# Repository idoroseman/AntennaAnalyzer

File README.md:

# Antenna Analyzer

The antenna analyzer will provide VSWR measurements for any antenna from 1 to 30 MHz. 
Frequency and VSWR are shown as a graph on the graphical display, as well as the minimum 
VSWR value and frequency.
The analyzer can be programmed to scan any sub band and has built in ranges for 160m, 80m, 60m, 40m, 30m, 20m, 17m, 15m, 12m, 10m. 

Derivative work of K6BEZ [project website](http://www.360workbench.com/) 

more details about construction on [my website](http://idoroseman.com/?p=841)

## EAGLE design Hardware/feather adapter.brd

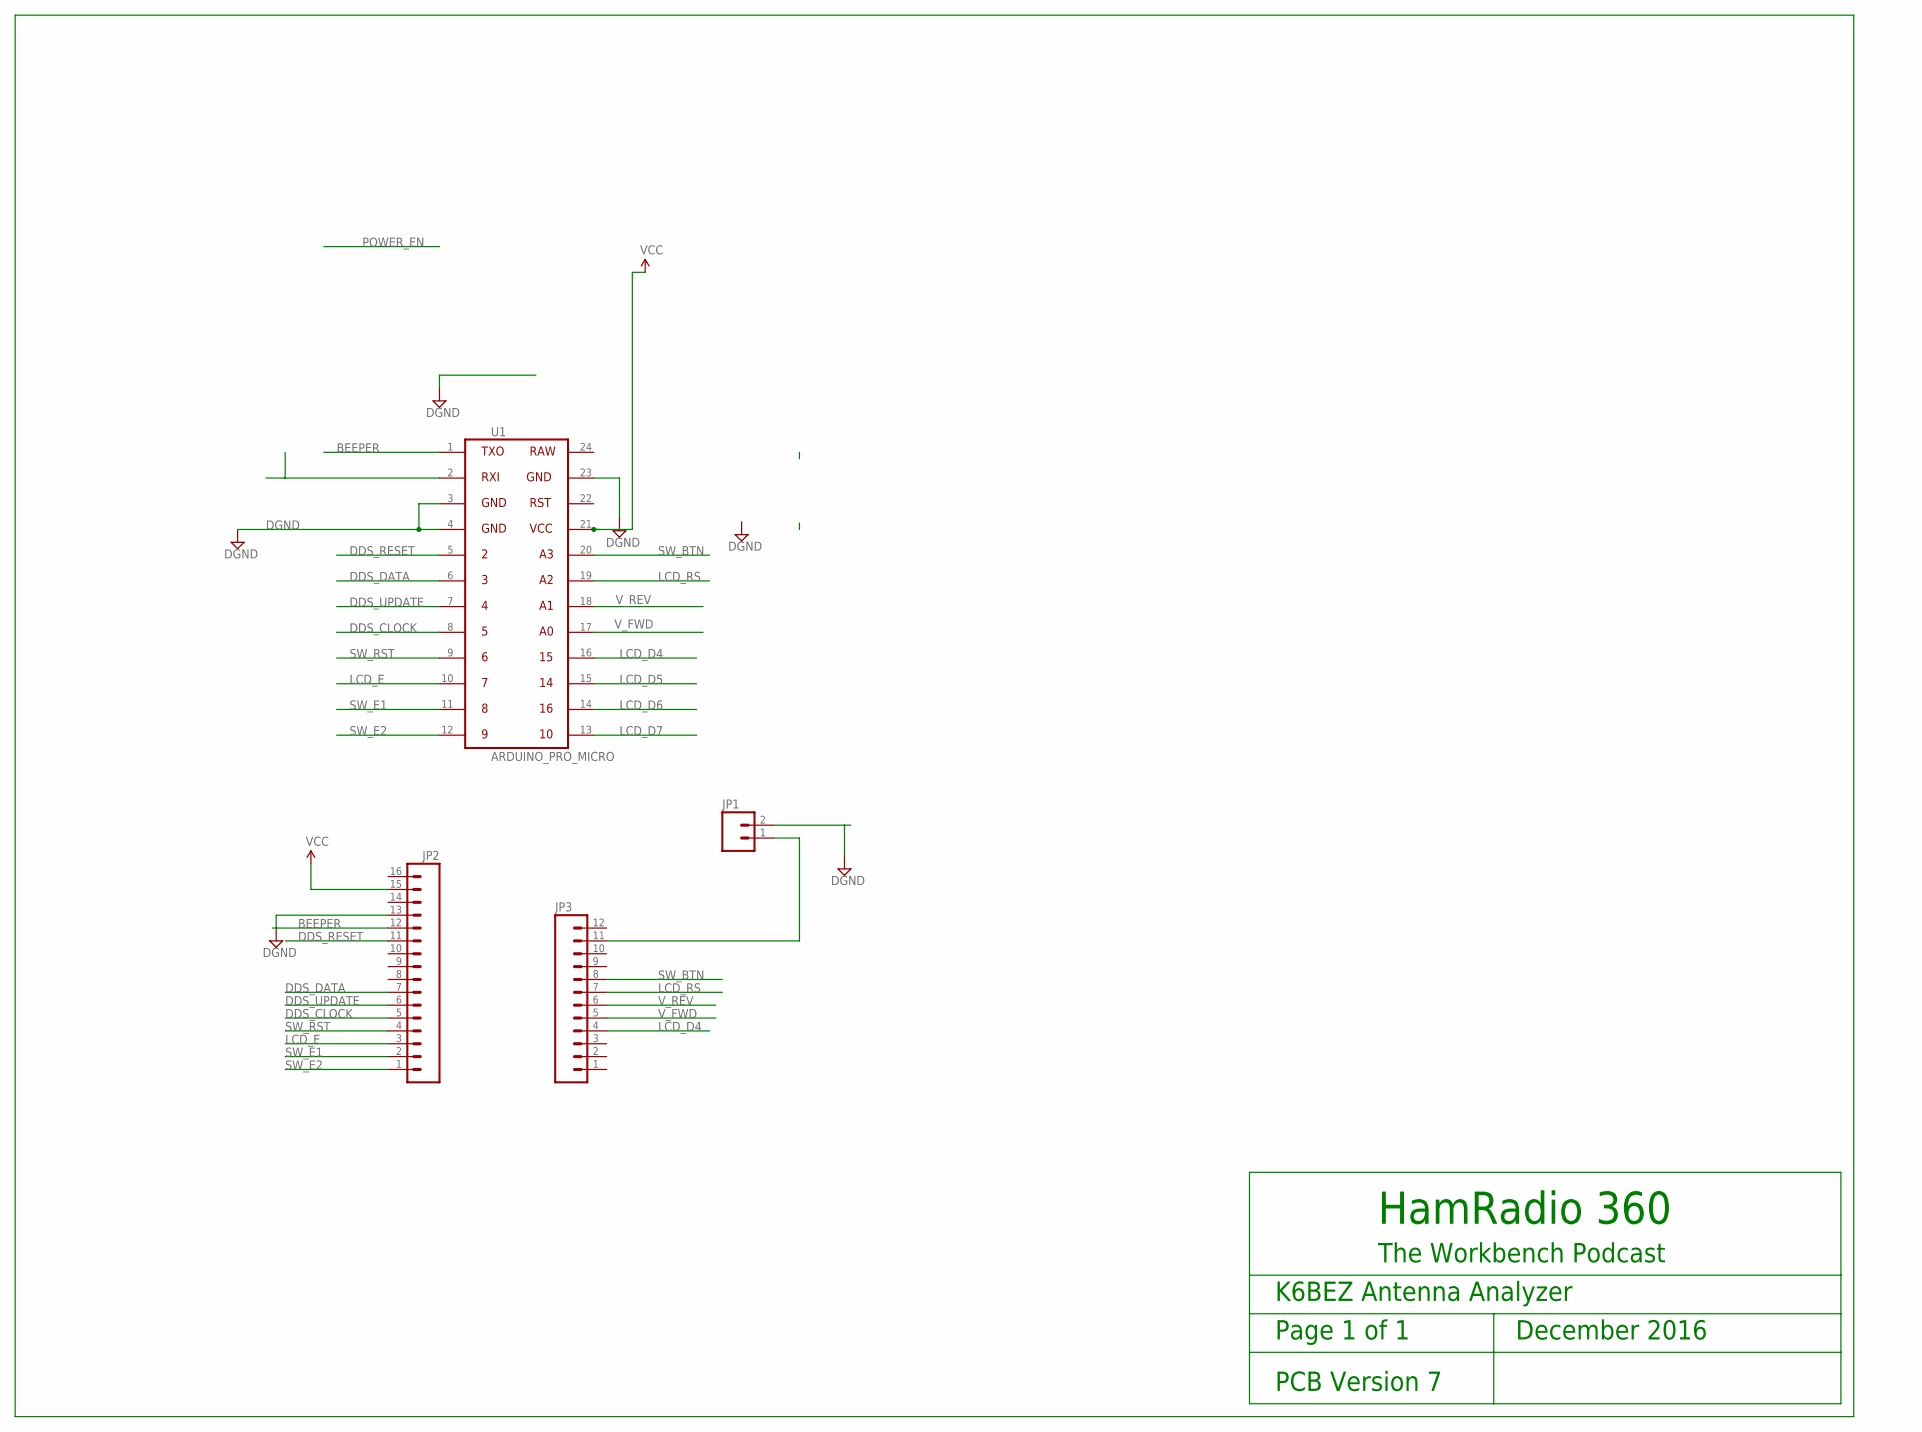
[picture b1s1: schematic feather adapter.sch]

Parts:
JP1: M02PTH; 1X02
JP2: M16PTH; 1X16
JP3: M12PTH; 1X12
U1: ARDUINO_PRO_MICRO

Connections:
BEEPER: JP2.12, U1.1
DDS_CLOCK: JP2.5, U1.8
DDS_DATA: JP2.7, U1.6
DDS_RESET: JP2.11, U1.5
DDS_UPDATE: JP2.6, U1.7
DGND: JP1.2, JP2.13, U1.3, U1.4, U1.23
LCD_D4: JP3.4, U1.16
LCD_D5: U1.15
LCD_D6: U1.14
LCD_D7: U1.13
LCD_E: JP2.3, U1.10
LCD_RS: JP3.7, U1.19
unnamed: JP1.1, JP3.11
SW_BTN: JP3.8, U1.20
SW_E1: JP2.2, U1.11
SW_E2: JP2.1, U1.12
SW_RST: JP2.4, U1.9
VCC: JP2.15, U1.21
V_FWD: JP3.5, U1.17
V_REV: JP3.6, U1.18

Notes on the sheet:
HamRadio 360
The Workbench Podcast
K6BEZ Antenna Analyzer
Page 1 of 1 December 2016
PCB Version 7

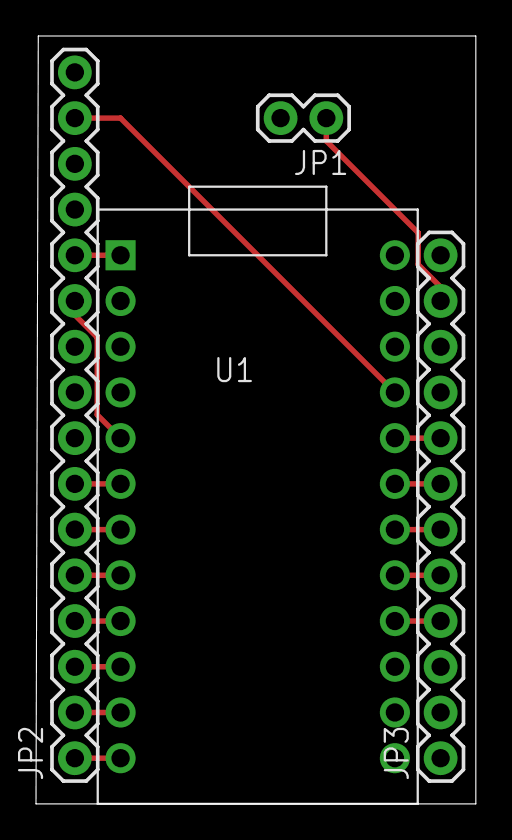
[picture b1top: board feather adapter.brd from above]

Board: 2 copper layers, 24.4 x 42.7 mm, 4 parts (0 on the bottom side), 17 nets.

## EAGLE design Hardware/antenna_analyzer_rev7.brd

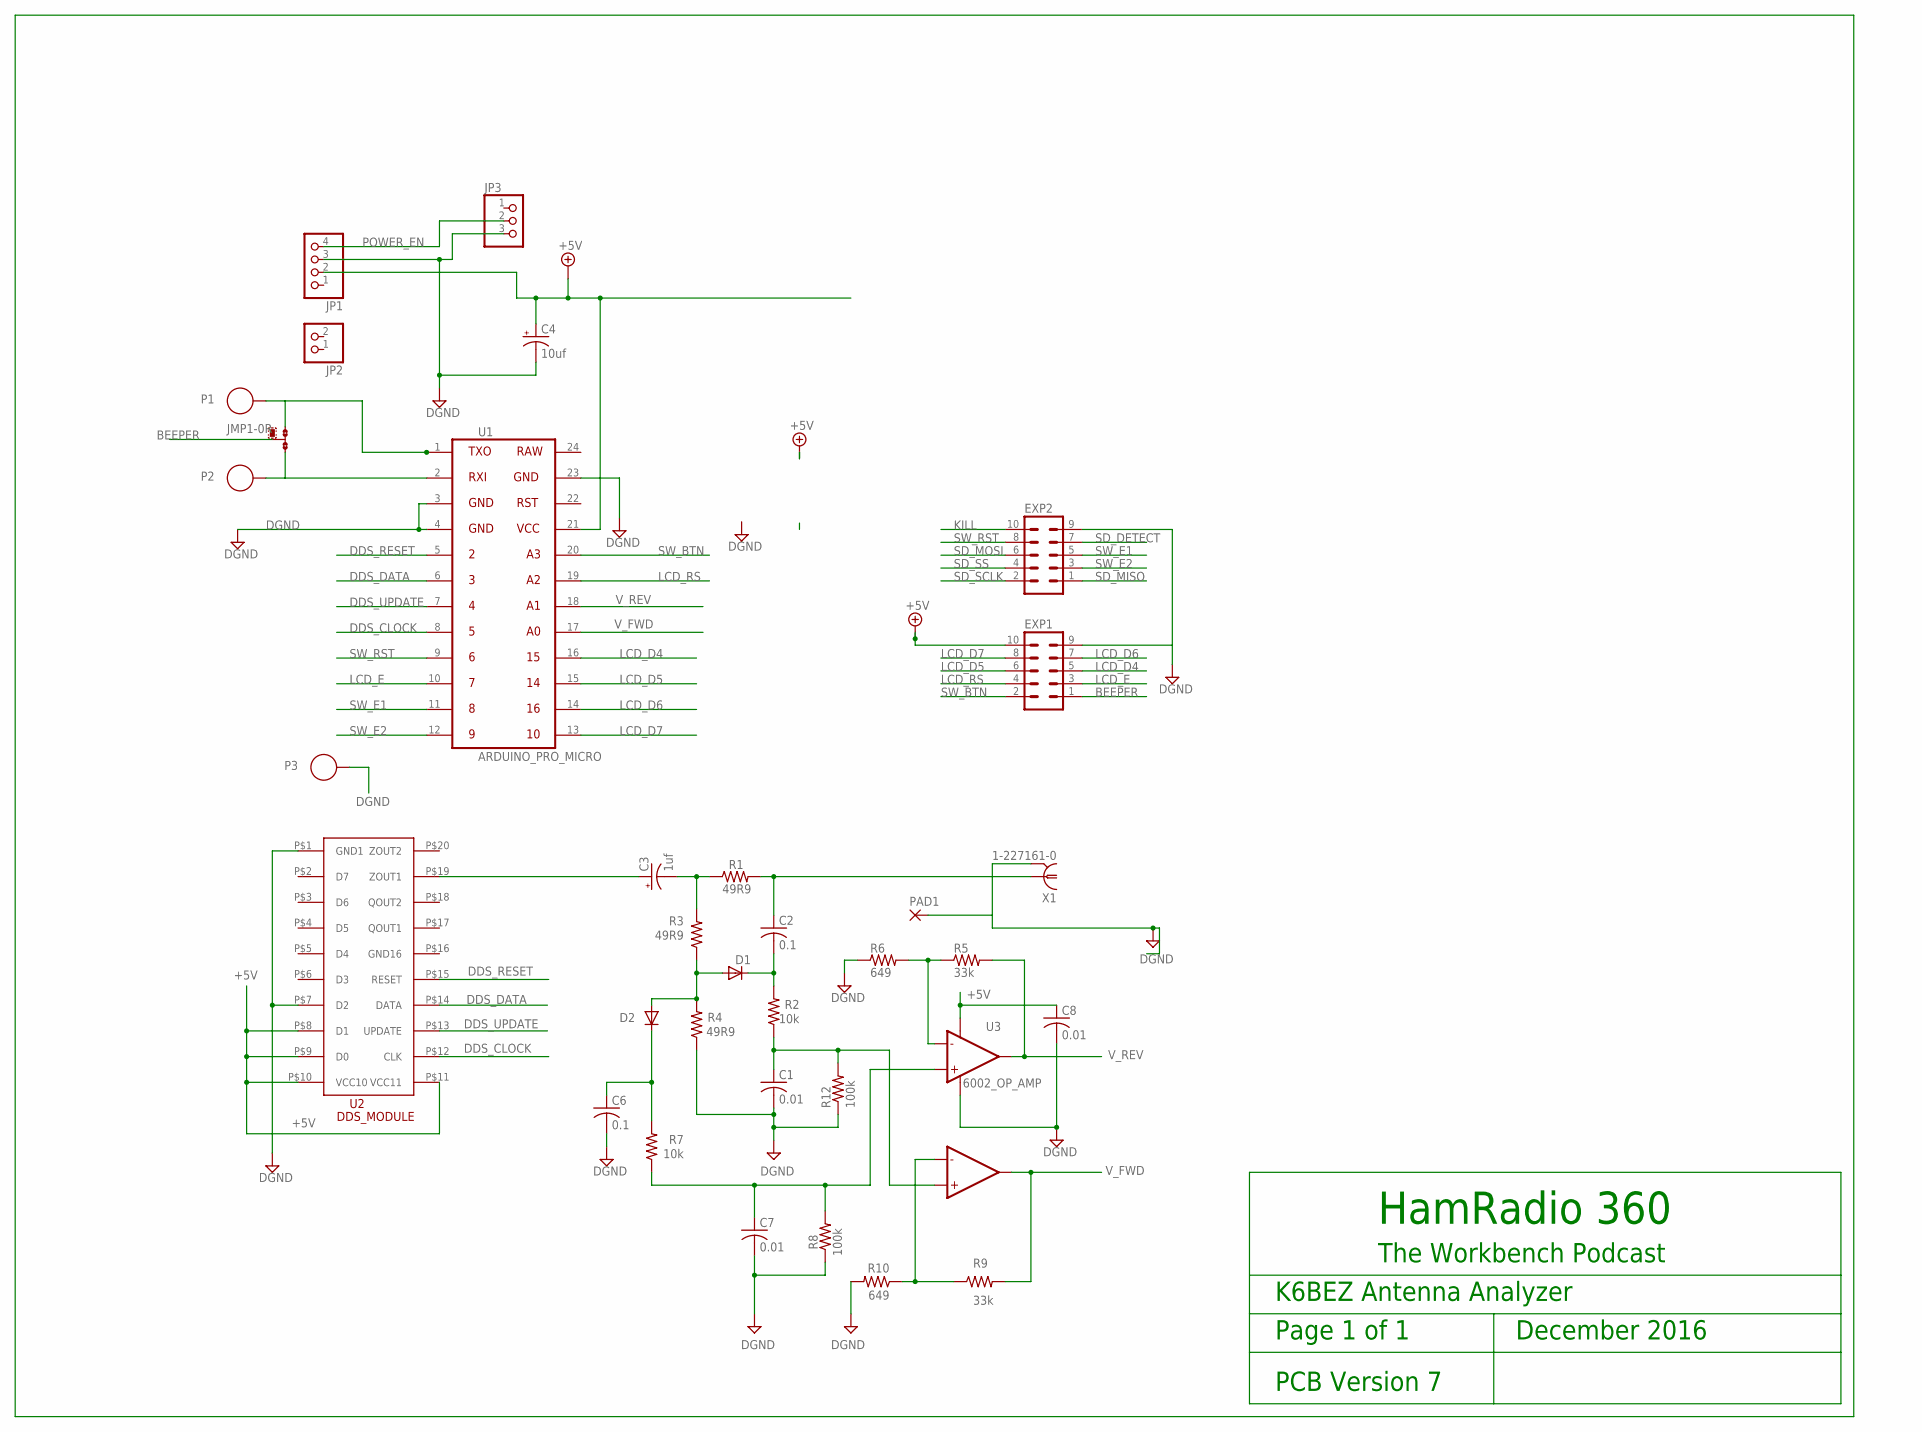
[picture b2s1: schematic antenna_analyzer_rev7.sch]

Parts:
C1, C7, C8: 0.01; C025-025X050
C2, C6: 0.1; C025-025X050
C3: 1uf; E1,8-4
C4: 10uf; E1,8-4
D1, D2: AA143; DO35-7
EXP1, EXP2: MA05-2
JMP1: 0R-JUMPA; A0R-JMP
JP1: PINHD-1X4; 1X04
JP2: PINHD-1X2; 1X02
JP3: PINHD-1X3; 1X03
P1, P2, P3: SOLDER_PAD_35_HOLE
PAD1: 1,6/0,9
R1, R3, R4: 49R9; 0207/10
R2, R7: 10k; 0207/10
R5, R9: 33k; 0207/10
R6, R10: 649; 0207/10
R8, R12: 100k; 0207/10
U1: ARDUINO_PRO_MICRO
U2: AD9850_MOD; DDS_DIL
U3: 6002_OP_AMP; OP_AMP_8_PIN
X1: 1-227161-0; AMP_227161

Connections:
+5V: C4.+, C8.1, EXP1.10, JP1.2, U1.21, U2.P$8 (D1), U2.P$9 (D0), U2.P$10 (VCC10), U2.P$11 (VCC11), U3.8 (VCC+)
BEEPER: EXP1.1, JMP1.2
DDS_CLOCK: U1.8, U2.P$12 (CLK)
DDS_DATA: U1.6, U2.P$14 (DATA)
DDS_RESET: U1.5, U2.P$15 (RESET)
DDS_UPDATE: U1.7, U2.P$13 (UPDATE)
DGND: C1.2, C4.-, C6.2, C7.2, C8.2, EXP1.9, EXP2.9, JP1.3, JP3.3, P3.1, PAD1.1, R4.1, R6.1, R8.1, R10.2, R12.1, U1.3, U1.4, U1.23, U2.P$1 (GND1), U2.P$7 (D2), U3.4 (VCC-), X1.2
KILL: EXP2.10
LCD_D4: EXP1.5, U1.16
LCD_D5: EXP1.6, U1.15
LCD_D6: EXP1.7, U1.14
LCD_D7: EXP1.8, U1.13
LCD_E: EXP1.3, U1.10
LCD_RS: EXP1.4, U1.19
unnamed: JMP1.1, P1.1, U1.1
unnamed: C6.1, D2.C, R7.2
unnamed: C3.+, U2.P$19 (ZOUT1)
unnamed: C3.-, R1.1, R3.2
unnamed: D1.A, D2.A, R3.1, R4.2
unnamed: C2.1, R1.2, X1.1
unnamed: JMP1.3, P2.1, U1.2
unnamed: C2.2, D1.C, R2.2
unnamed: C1.1, R2.1, R12.2, U3.5 (IN+2)
unnamed: C7.1, R7.1, R8.2, U3.3 (IN+1)
unnamed: R9.1, R10.1, U3.6 (IN-2)
unnamed: R5.1, R6.2, U3.2 (IN-1)
POWER_EN: JP1.4, JP3.2
SD_DETECT: EXP2.7
SD_MISO: EXP2.1
SD_MOSI: EXP2.6
SD_SCLK: EXP2.2
SD_SS: EXP2.4
SW_BTN: EXP1.2, U1.20
SW_E1: EXP2.5, U1.11
SW_E2: EXP2.3, U1.12
SW_RST: EXP2.8, U1.9
V_FWD: R9.2, U1.17, U3.7 (OUT2)
V_REV: R5.2, U1.18, U3.1 (OUT1)

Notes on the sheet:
HamRadio 360
The Workbench Podcast
K6BEZ Antenna Analyzer
Page 1 of 1 December 2016
PCB Version 7

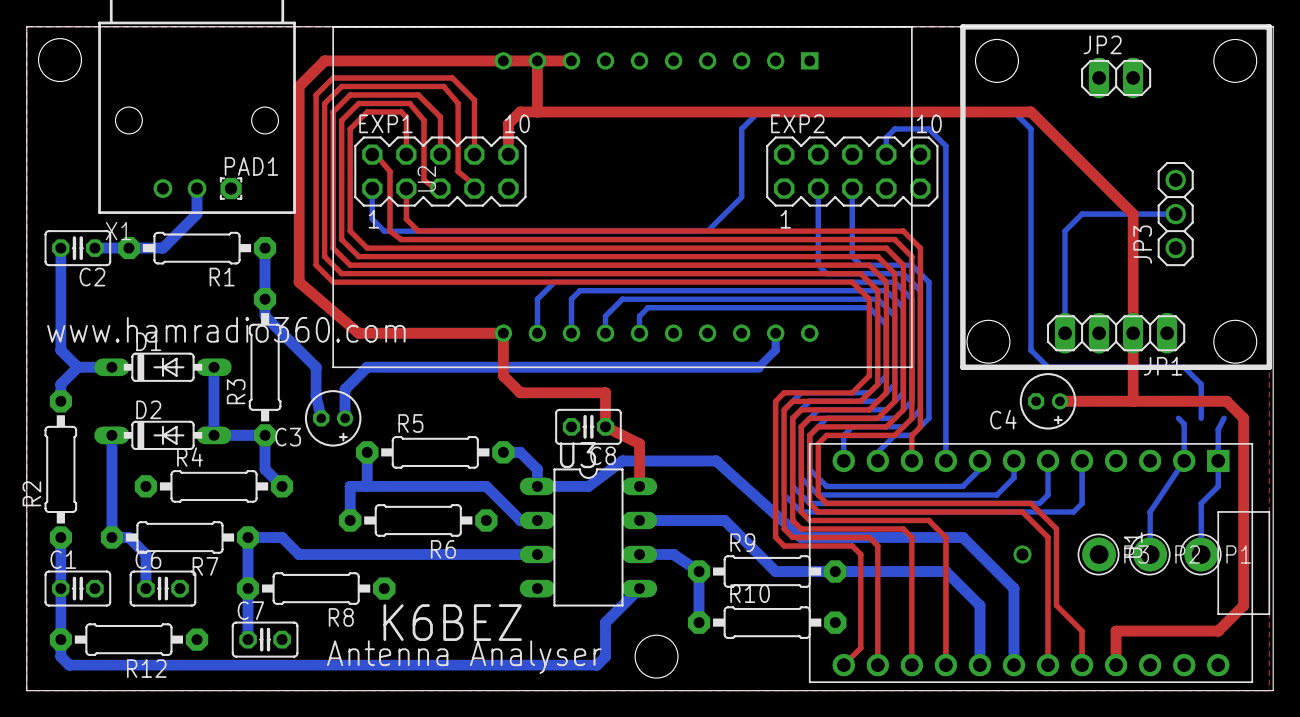
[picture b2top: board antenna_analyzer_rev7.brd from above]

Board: 2 copper layers, 93.0 x 49.5 mm, 34 parts (1 on the bottom side), 32 nets.

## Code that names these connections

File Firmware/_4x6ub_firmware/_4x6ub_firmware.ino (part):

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#include <U8g2lib.h>
#include <RotaryEncoder.h>

#define LCD_E   7
#define LCD_D4  15
#define LCD_RS  A2

#define DDS_RESET 2
#define DDS_SDAT 3
#define DDS_UPDATE 4
#define DDS_SCLK 5

#define MODE A2
#define BAND A3

#define SW_RST  6
#define SW_E1   9
#define SW_E2   8
#define SW_BTN  A3

#define BUZZER  10
#define LED_INTERNAL 17
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#define DEBOUNCE 10

// initialize the library with the numbers of the interface pins
U8G2_ST7920_128X64_1_SW_SPI u8g2(U8G2_R0, /* clock=*/ LCD_D4, /* data=*/ LCD_E, /* CS=*/ LCD_RS, /* reset=*/ U8X8_PIN_NONE);
RotaryEncoder encoder(SW_E2, SW_E1);

long num_steps = 100;      // Number of steps to use in the sweep
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  Serial.begin(115200);

  // Configure DDS control pins for digital output
  pinMode(DDS_UPDATE, OUTPUT);
  pinMode(DDS_SCLK, OUTPUT);
  pinMode(DDS_SDAT, OUTPUT);
  pinMode(DDS_RESET, OUTPUT);

  // Set up analog inputs on A0 and A1, internal reference voltage
  pinMode(AREV, INPUT);
  pinMode(AFWD, INPUT);
  analogReference(DEFAULT);

  pinMode(SW_RST, INPUT_PULLUP); 
  pinMode(SW_BTN, INPUT_PULLUP); 
  pinMode(SW_E1, INPUT_PULLUP); 
  pinMode(SW_E2, INPUT_PULLUP);
  pinMode(BUZZER, OUTPUT);
  
  // Reset the DDS
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
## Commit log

2020-12-17 switch to git

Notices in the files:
parts and their libraries:
SparkFun-Connectors: Licensing: Creative Commons ShareAlike 4.0 International - https://creativecommons.org/licenses/by-sa/4.0
